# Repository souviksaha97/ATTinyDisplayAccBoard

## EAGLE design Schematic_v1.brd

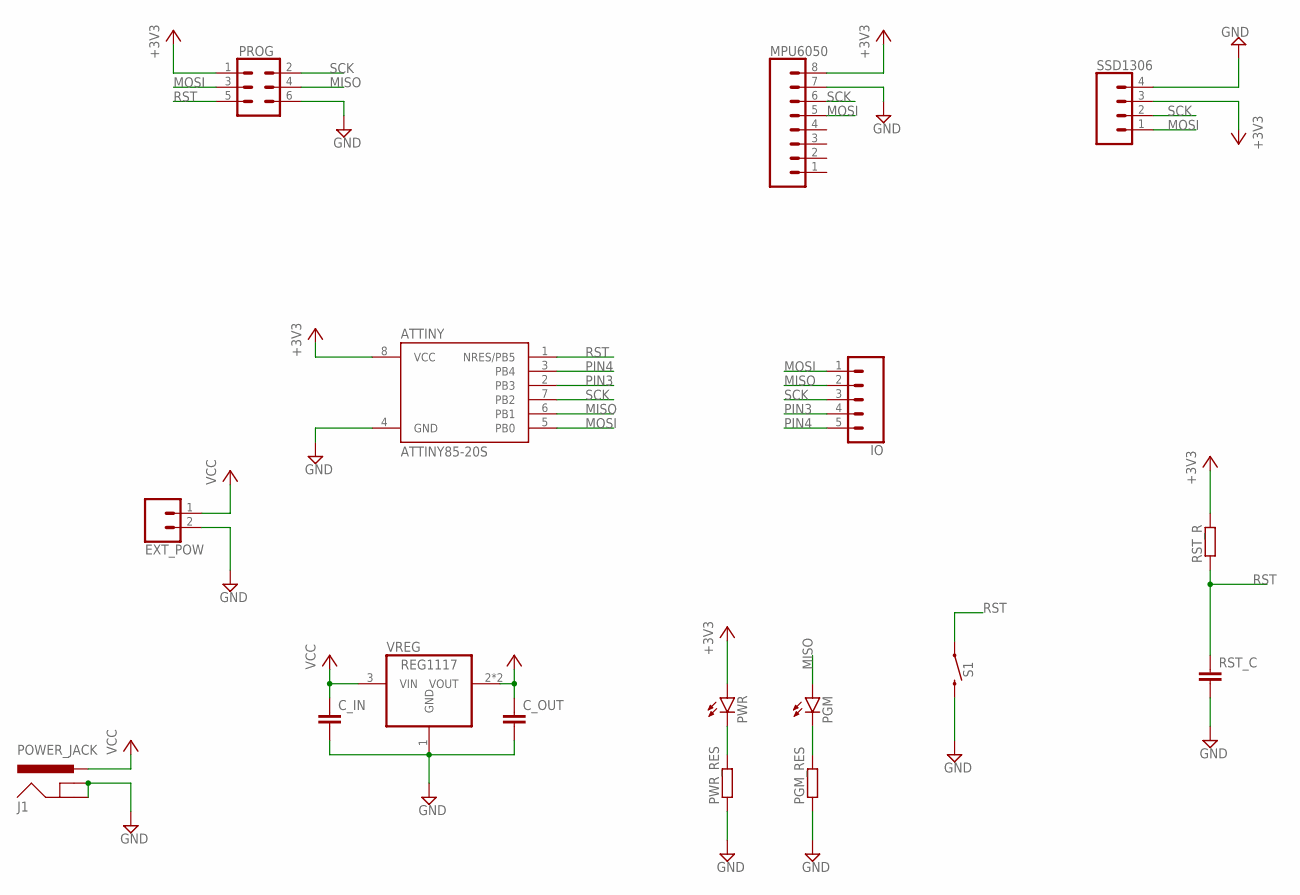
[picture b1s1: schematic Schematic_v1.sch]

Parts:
ATTINY: ATTINY85-20S; SOIC8_EIAJ_208MIL
C_IN: C-EUC1206; C1206
C_OUT: C-EUC1206; C1206
EXT_POW: CONN_021X02_NO_SILK; 1X02_NO_SILK
IO: CONN_05; 1X05
J1: POWER_JACK; POWER_JACK_PTH
MPU6050: CONN_08"; 1X08
PGM: LEDSML1206; SML1206
PGM_RES: R-EU_R1206; R1206
PROG: CONN_03X2NO_SILK; 2X3-NS
PWR: LEDSML1206; SML1206
PWR_RES: R-EU_R1206; R1206
RST_C: C-EUC1206; C1206
RST_R: R-EU_R1206; R1206
S1: MOMENTARY-SWITCH-SPST-PTH-6.0MM; TACTILE_SWITCH_PTH_6.0MM
SSD1306: CONN_04; 1X04
VREG: REG1117; SOT223

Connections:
+3V3: ATTINY.8 (VCC), C_OUT.1, MPU6050.8, PROG.1, PWR.A, RST_R.2, SSD1306.3, VREG.2 (VOUT), VREG.4 (VOUT)
GND: ATTINY.4 (GND), C_IN.2, C_OUT.2, EXT_POW.2, J1.GND, J1.GNDBREAK, MPU6050.7, PGM_RES.1, PROG.6, PWR_RES.1, RST_C.2, S1.3 (2), SSD1306.4, VREG.1 (GND)
MISO: ATTINY.6 (PB1), IO.2, PGM.A, PROG.4
MOSI: ATTINY.5 (PB0), IO.1, MPU6050.5, PROG.3, SSD1306.1
unnamed: PWR.C, PWR_RES.2
unnamed: PGM.C, PGM_RES.2
PIN3: ATTINY.2 (PB3), IO.4
PIN4: ATTINY.3 (PB4), IO.5
RST: ATTINY.1 (NRES/PB5), PROG.5, RST_C.1, RST_R.1, S1.1
SCK: ATTINY.7 (PB2), IO.3, MPU6050.6, PROG.2, SSD1306.2
VCC: C_IN.1, EXT_POW.1, J1.PWR, VREG.3 (VIN)

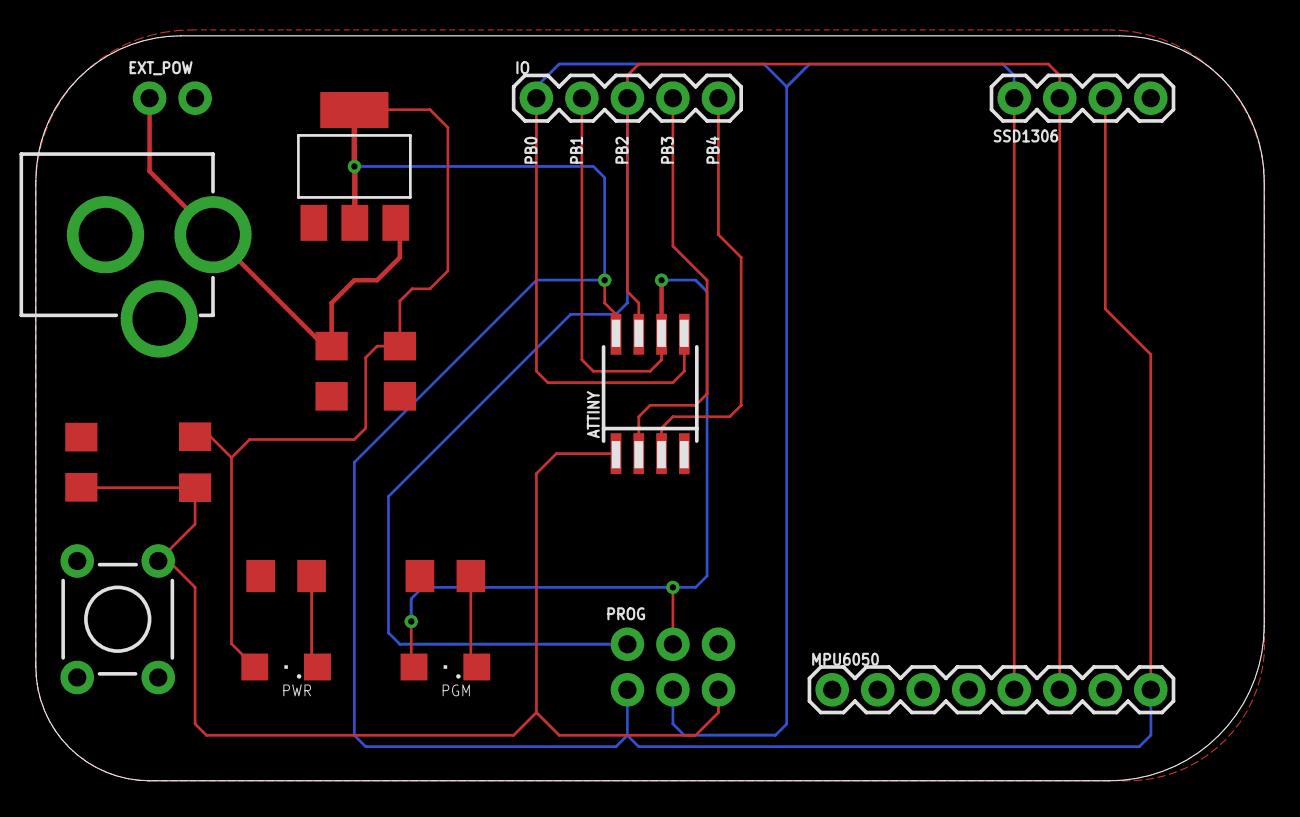
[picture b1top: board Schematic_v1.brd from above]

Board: 2 copper layers, 68.6 x 41.6 mm, 17 parts (0 on the bottom side), 11 nets.

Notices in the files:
parts and their libraries:
SparkFun-Connectors: Licensing: Creative Commons ShareAlike 4.0 International - https://creativecommons.org/licenses/by-sa/4.0
